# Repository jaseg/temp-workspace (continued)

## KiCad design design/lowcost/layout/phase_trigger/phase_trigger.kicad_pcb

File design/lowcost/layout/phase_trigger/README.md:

# Layout fragment: phase_trigger (trigger path, line driver, 16-tap phase delay line) - re-layout
`python3 gen_phase_trigger.py` -> `phase_trigger.kicad_pcb` (KiCad 7, 105.1 x 25.4 mm, own Edge.Cuts) and prints all tables and checks below.
`phase_trigger.png`: top = F.Cu without the pour (so widths show), silk, fab; below: F.Cu with pour, B.Cu (mirrored), In1, In2.
`phase_trigger_detail.png`: tap cells and one comparator, F.Cu red and B.Cu blue. Values: `sim/phase`, `sim/phase_array` RESULT.md, SPEC 4-6, 9.

## Stack-up (SPEC decision 9 rev., written into the board setup)
JLC04161H-7628 1.6 mm, checked on jlcpcb.com/impedance: F.Cu 35 um / 7628 0.2104 mm er 4.4 / In1 = solid GND / core 1.065 mm /
In2 = power (+2V5, +3V3, VTAP_N / VTAP_P strips) / 7628 0.2104 mm / B.Cu (GND pour, -2V5 and VSW_GND polygons, slow nets).
Mask er 3.8, 15 um on the trace. `microstrip()` = Hammerstad-Jensen + thickness correction + first-order mask term; `cpwg()` = Wadell.
| Line | width | Z0 | eps_eff | delay |
|---|---|---|---|---|
| 50 R (all 50 R nets, feeds, terminations) | **0.36 mm** (exact 0.360) | 50.0 R (51.0 R without mask) | 3.30 | 6.057 ps/mm |
| PSTRB_A/K sections, 73 R | **0.16 mm** (exact 0.159) | 72.8 R | 3.08 | 5.852 ps/mm |
| PH_LINE sections (width chosen for loaded 50 R) | **0.25 mm** (exact 0.251) | 60.1 R | 3.19 | 5.959 ps/mm |
Coplanar check: the side pour only lowers Z for gaps < 0.33 mm; pour gap used = 2 w (0.72 / 0.32 / 0.50 mm) -> microstrip, no correction.
Top pour keep-outs at 2 w around every RF segment and pad (script-verified on the filled pour); no pour between the strobe lines.
## Delay line (every cell generated by the same code, spread 0.000 ps)
| line | section | Z0 | load / tap | length / tap | unloaded | loaded | loaded Z |
|---|---|---|---|---|---|---|---|
| PSTRB_A/K | 0.16 mm straight | 72.8 R | 0.40 gate + 0.049 cap pad + 0.02 resistor fringe = 0.469 pF | **4.514 mm = pitch** | 26.4 ps | **40.0 ps** | 48.1 R |
| PH_LINE | 0.26 mm S-meander | 59.0 R | 0.37 gate + 0.026 pin-3 pad = 0.396 pF | **9.929 mm** | 59.3 ps | **70.0 ps** | 50.0 R |
PH_LINE targets 70 ps and the strobe lines 40 ps per tap (phase_array/RESULT: a 70 ps design measured 75.7 ps) -> expected ~75 ps real, 35 ps effective. The per-tap delays were raised from 65 / 35 ps so that the pitch (4.514 mm) leaves room for the meander: pin-3 pad edge to the nearest meander leg 0.52 mm, leg to leg 0.51 mm (was 0.02 / 0.244 mm). The 40 / 75 ps combination is not re-simulated.
Note: for a 70 ps section the trace that loads to 50 R is 60 R, not 73 R (73 R belonged to the 24 ps sections of phase/RESULT).
Cell: BAT15-04W, PH_LINE enters between pins 1/2 under the body and ends in pin 3 (zero-length tap), leaves pin 3 downward into an
S-meander (legs x = 1.00 / 1.99 / 2.76 mm, half-height 1.50 mm, same-net gaps >= 0.5 mm), 45-degree landing into the next diode. All on F.Cu
over In1, **no vias in any RF path**. Hold caps CA/CK vertical, node pad 0.29 mm from pin 1/2 (0.15 mm node trace), outer pad on the
strobe line. 1 k (to the comparator) and 2.2 k (to VTAP via In2) straddle each strobe line, perpendicular, either side of the cap.
**Summing node (symmetric)**: the A-side and K-side 1 k resistors are mirror images; each outer pad has a via (0.605 mm F.Cu) and the two
vias are joined by a straight B.Cu jumper (2 x 3.835 mm). The comparator input is tapped from the jumper MIDPOINT: a B.Cu branch runs
0.8 mm west of the jumper to its own via (4.166 mm), then F.Cu to the comparator pin. Both resistors therefore see the same path and stray
capacitance. Each COS3502 is centred between its two tap vias, so the routes to pins 1 and 3 are mirror images (3.849 mm each); the
script asserts channel A = channel B. One extra via per tap.
In1 cut-out under each hold node (VTAP strip in In2 below instead, symmetric A/K). K-side 1 k joins the A side on B.Cu (DC node).
COS3502 row behind PSTRB_A: pin 1 in line with the tap's 1 k, IN- via to the B.Cu VTH rail (R404 1 k / C404 100 n from VTAP_TH).

## Main chain (y = 0, in line, 0.3-0.35 mm pad gaps)
X1 BUF_OUT_T / J301 SMA (49.9 R R301 at U301.3) -> U301 TMUX136 -> TRIG_COM 3.0 mm -> U302 TLV3801 -> CMP_P / CMP_N as 2 x 50 R
(0.6 mm gap), R307 100 R bridging, R309/R310 470 R taps (LVDS_A under CMP_N on B.Cu) -> C308 -> U303 TRF37D73 -> bias tee -> C309 -> pi pad R311/R312/R313 -> 0.36 -> 0.25 mm step at x = -1.6 -> D01. PSTRB feeds from X2/X3
(50 R, 3.84 mm) step to 0.16 mm half a pitch before tap 0; far end 0.36 mm into 49.9 R (R401, R402, R403).
**Bias tee (revised, `sim/bias_tee/RESULT.md`, `bias_tee_detail.png` before/after)**: FB301 BLM15HD102 with pad 1 centred ON the line
-> 0.64 mm link -> L302 47 uH LQH32CN470K23L 1210 with R382 1 k beside it -> C314 100 nF across the cold pad (GND via at its pad) ->
+3V3 plane via pair beyond C314, TP306 on that row; C311/C312 moved 0.25 mm left to make room. Was 120 nH + 47 uH 0806 (on a 1008
land) + 100 n / 1 n beside it: 11 dB suck-out at 313 MHz, PRBS DDJ 17 ps rms; C313 (1 nF at the cold end, useless there) removed.
Necks: none (0.36 mm traces end on the WSON/UQFN pin centres with >= 0.19 mm to the neighbour pins).
Pad discontinuities (excess C vs line): 0402 in-line / T pads +28 fF, WSON/UQFN pins -11 fF, SOT-323 pin 3 +28 fF and hold-cap
pad +49 fF (both inside the tap load). SMA pin (1.27 mm): In1 cut-out below -> 70 R over 1.8 mm instead of +314 fF.

## Supplies and vias
Each supply pin -> 0.25-0.6 mm copper -> decoupling cap at the pin -> via pair to the In2 plane; -2V5 (TLV EP vias, R304, R306)
and VSW_GND (TMUX) as B.Cu polygons, VSW_GND pins also on a local F.Cu polygon; TRF EP 3 vias. Ground pads: one via beside
the pad. 182 vias: 46 GND, 69 supply, 67 signal (TAPn_IN, VTH, LVDS_A); **no stitching grid, no fences** (stitch after assembly).

**Changed vs previous**: JLC04161H-3313 -> 7628; all widths from the formula; PH_LINE moved from B.Cu (2 vias per tap) to an F.Cu meander; strobe 0.09 ->
0.16 mm (73 R now possible), pitch 3.815 -> 4.514 mm (40 ps per tap); compact in-line chain; no 90-degree corners; power via planes/polygons;
588 stitching vias removed; outline 106.8 x 24.6 -> 105.1 x 25.4 mm.

## Checks and open points
Script: bends <= 45 deg everywhere (corners at pad centres excepted), 0.1 mm copper clearance OK, passive courtyards OK, own
connectivity check 0 unrouted, RF pour clearance OK. 21 decoupling/chain parts sit inside the IC courtyard margin (pad gap >= 0.25 mm).
**kicad-cli 7 has no DRC**: run DRC in pcbnew after integration. U301 COM2 open on purpose.
Open: 40 / 75 ps per tap is not re-simulated (sim/phase_array used 35 / 70 ps); meander self-coupling is small at 0.5 mm gaps (2.4 h) but check by TDR.
Loaded strobe Z 45.5 R vs 49.9 R terminations (5 % reflection). Left 1 k inner pad of each node is over ground (~0.06 pF).
VTAP decoupling only at both ends of the In2 strips (DC rail behind 2.2 k). Corner WSON pins entered along x, not the pad axis.

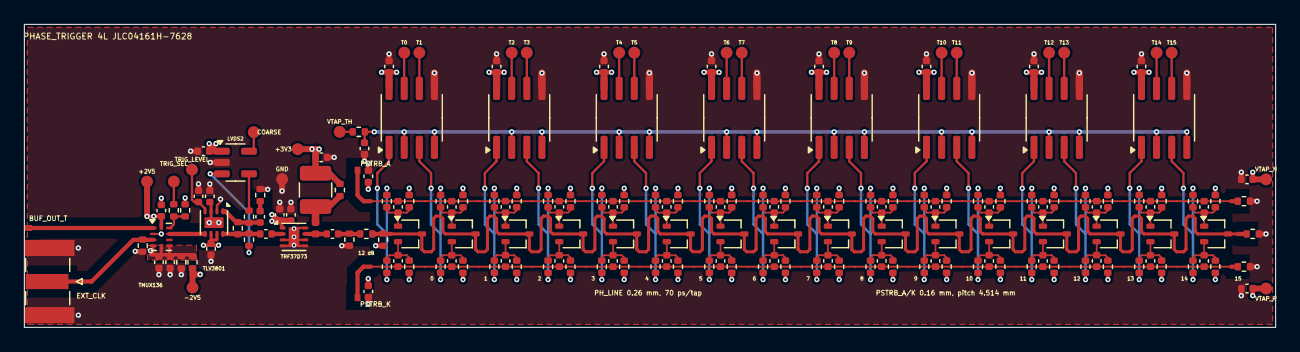
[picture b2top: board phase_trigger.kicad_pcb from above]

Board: 4 copper layers, 105.1 x 25.4 mm, 199 parts (0 on the bottom side), 92 nets.

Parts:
C30, C31, C32, C33, C34, C35, C36, C37, C301, C302, C304, C305, C310, C312, C314, C404: 100n; C_0402_1005Metric
C303, C311: 1n C0G; C_0402_1005Metric
C306: 10n; C_0402_1005Metric
C307, C308, C309: 1u; C_0402_1005Metric
CA00, CA01, CA02, CA03, CA04, CA05, CA06, CA07, CA08, CA09, CA10, CA11, CA12, CA13, CA14, CA15: 0.47p C0G; C_0402_1005Metric
CK00, CK01, CK02, CK03, CK04, CK05, CK06, CK07, CK08, CK09, CK10, CK11, CK12, CK13, CK14, CK15: 0.47p C0G; C_0402_1005Metric
CN00, CN15: 100n; C_0402_1005Metric
CP00, CP15: 100n; C_0402_1005Metric
D01, D02, D03, D04, D05, D06, D07, D08, D09, D10, D11, D12, D13, D14, D15, D16: BAT15-04W; SOT-323_SC-70
FB301: BLM15HD102; L_0402_1005Metric
J301: SMA EXT_CLK; SMA_Samtec_SMA-J-P-X-ST-EM1_EdgeMount
L302: 47u LQH32CN; L_1210_3225Metric
R301, R308, R401, R402, R403: 49.9; R_0402_1005Metric
R303: 1.5k; R_0402_1005Metric
R304: 2.7k; R_0402_1005Metric
R305: 10k; R_0402_1005Metric
R306: 18k; R_0402_1005Metric
R307: 100; R_0402_1005Metric
R309, R310: 470; R_0402_1005Metric
R311, R313: 82; R_0402_1005Metric
R312: 91; R_0402_1005Metric
R382, R404: 1k; R_0402_1005Metric
RNA00, RNA01, RNA02, RNA03, RNA04, RNA05, RNA06, RNA07, RNA08, RNA09, RNA10, RNA11, RNA12, RNA13, RNA14, RNA15: 2.2k; R_0402_1005Metric
RNK00, RNK01, RNK02, RNK03, RNK04, RNK05, RNK06, RNK07, RNK08, RNK09, RNK10, RNK11, RNK12, RNK13, RNK14, RNK15: 2.2k; R_0402_1005Metric
RSA00, RSA01, RSA02, RSA03, RSA04, RSA05, RSA06, RSA07, RSA08, RSA09, RSA10, RSA11, RSA12, RSA13, RSA14, RSA15: 1k; R_0402_1005Metric
RSK00, RSK01, RSK02, RSK03, RSK04, RSK05, RSK06, RSK07, RSK08, RSK09, RSK10, RSK11, RSK12, RSK13, RSK14, RSK15: 1k; R_0402_1005Metric
TP301, TP302, TP303, TP304, TP305, TP306, TP307, TP401, TP402, TP403, TP500, TP501, TP502, TP503, TP504, TP505, TP506, TP507, TP508, TP509, TP510, TP511, TP512, TP513, TP514, TP515: TestPoint_Pad_D1.0mm
U11, U12, U13, U14, U15, U16, U17, U18: COS3502; SOIC-8_3.9x4.9mm_P1.27mm
U301: TMUX136; Texas_UQFN-10_1.5x2mm_P0.5mm
U302: TLV3801; WSON-8-1EP_2x2mm_P0.5mm_EP0.9x1.6mm
U303: TRF37D73; WSON-8-1EP_2x2mm_P0.5mm_EP0.9x1.6mm
U304: SN65LVDS2; SOT-23-5
X1: IF_BUF_OUT_T
X2: IF_PSTRB_A
X3: IF_PSTRB_K

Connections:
+2V5: C301.1, C304.2, TP304.1, U301.10, U302.6, U302.7
+3V3: C30.1, C31.1, C32.1, C33.1, C34.1, C35.1, C36.1, C37.1, C310.2, C311.1, C312.1, C314.1, L302.2, R382.2, TP306.1, U11.8, U12.8, U13.8, U14.8, U15.8, U16.8, U17.8, U18.8, U303.1, U304.1
-2V5: C305.1, R304.1, R306.2, TP303.1, U302.3, U302.9
BUF_OUT_T: U301.1, X1.1
CMP_N: C307.1, R307.2, R310.1, U302.1
CMP_N_DUM: C307.2, R308.1
CMP_P: C308.1, R307.1, R309.2, U302.8
COARSE: TP305.1, U304.5
EXT_CLK: J301.1, R301.2, U301.3
GND: C30.2, C31.2, C32.2, C33.2, C34.2, C35.2, C36.2, C37.2, C302.1, C303.1, C304.1, C305.2, C306.2, C310.1, C311.2, C312.2, C314.2, C404.1, CN00.2, CN15.1, CP00.1, CP15.1, J301.2, R301.1, R303.1, R308.2, R311.1, R313.1, R401.2, R402.2, R403.2, TP307.1, U11.5, U12.5, U13.5, U14.5, U15.5, U16.5, U17.5, U18.5, U302.2, U303.3, U303.4, U303.5, U303.6, U303.8, U303.9, U304.2
LVDS_A: R309.1, U304.3
LVDS_B: R310.2, U304.4
PAD_IN: C309.2, R311.2, R312.1
PH_LINE: D01.3, D02.3, D03.3, D04.3, D05.3, D06.3, D07.3, D08.3, D09.3, D10.3, D11.3, D12.3, D13.3, D14.3, D15.3, D16.3, R312.2, R313.2, R401.1
PSTRB_A: CA00.2, CA01.2, CA02.2, CA03.2, CA04.2, CA05.2, CA06.2, CA07.2, CA08.2, CA09.2, CA10.2, CA11.2, CA12.2, CA13.2, CA14.2, CA15.2, R402.1, X2.1
PSTRB_K: CK00.1, CK01.1, CK02.1, CK03.1, CK04.1, CK05.1, CK06.1, CK07.1, CK08.1, CK09.1, CK10.1, CK11.1, CK12.1, CK13.1, CK14.1, CK15.1, R403.1, X3.1
TAP0: TP500.1, U11.7
TAP0_A: CA00.1, D01.1, RNA00.1, RSA00.1
TAP0_IN: RSA00.2, RSK00.1, U11.1
TAP0_K: CK00.2, D01.2, RNK00.2, RSK00.2
TAP1: TP501.1, U11.6
TAP1_A: CA01.1, D02.1, RNA01.1, RSA01.1
TAP1_IN: RSA01.2, RSK01.1, U11.3
TAP1_K: CK01.2, D02.2, RNK01.2, RSK01.2
TAP2: TP502.1, U12.7
TAP2_A: CA02.1, D03.1, RNA02.1, RSA02.1
TAP2_IN: RSA02.2, RSK02.1, U12.1
TAP2_K: CK02.2, D03.2, RNK02.2, RSK02.2
TAP3: TP503.1, U12.6
TAP3_A: CA03.1, D04.1, RNA03.1, RSA03.1
TAP3_IN: RSA03.2, RSK03.1, U12.3
TAP3_K: CK03.2, D04.2, RNK03.2, RSK03.2
TAP4: TP504.1, U13.7
TAP4_A: CA04.1, D05.1, RNA04.1, RSA04.1
TAP4_IN: RSA04.2, RSK04.1, U13.1
TAP4_K: CK04.2, D05.2, RNK04.2, RSK04.2
TAP5: TP505.1, U13.6
TAP5_A: CA05.1, D06.1, RNA05.1, RSA05.1
TAP5_IN: RSA05.2, RSK05.1, U13.3
TAP5_K: CK05.2, D06.2, RNK05.2, RSK05.2
TAP6: TP506.1, U14.7
TAP6_A: CA06.1, D07.1, RNA06.1, RSA06.1
TAP6_IN: RSA06.2, RSK06.1, U14.1
TAP6_K: CK06.2, D07.2, RNK06.2, RSK06.2
TAP7: TP507.1, U14.6
TAP7_A: CA07.1, D08.1, RNA07.1, RSA07.1
TAP7_IN: RSA07.2, RSK07.1, U14.3
TAP7_K: CK07.2, D08.2, RNK07.2, RSK07.2
TAP8: TP508.1, U15.7
TAP8_A: CA08.1, D09.1, RNA08.1, RSA08.1
TAP8_IN: RSA08.2, RSK08.1, U15.1
TAP8_K: CK08.2, D09.2, RNK08.2, RSK08.2
TAP9: TP509.1, U15.6
TAP9_A: CA09.1, D10.1, RNA09.1, RSA09.1
TAP9_IN: RSA09.2, RSK09.1, U15.3
TAP9_K: CK09.2, D10.2, RNK09.2, RSK09.2
TAP10: TP510.1, U16.7
TAP10_A: CA10.1, D11.1, RNA10.1, RSA10.1
TAP10_IN: RSA10.2, RSK10.1, U16.1
TAP10_K: CK10.2, D11.2, RNK10.2, RSK10.2
TAP11: TP511.1, U16.6
TAP11_A: CA11.1, D12.1, RNA11.1, RSA11.1
TAP11_IN: RSA11.2, RSK11.1, U16.3
TAP11_K: CK11.2, D12.2, RNK11.2, RSK11.2
TAP12: TP512.1, U17.7
TAP12_A: CA12.1, D13.1, RNA12.1, RSA12.1
TAP12_IN: RSA12.2, RSK12.1, U17.1
TAP12_K: CK12.2, D13.2, RNK12.2, RSK12.2
TAP13: TP513.1, U17.6
TAP13_A: CA13.1, D14.1, RNA13.1, RSA13.1
TAP13_IN: RSA13.2, RSK13.1, U17.3
TAP13_K: CK13.2, D14.2, RNK13.2, RSK13.2
TAP14: TP514.1, U18.7
TAP14_A: CA14.1, D15.1, RNA14.1, RSA14.1
TAP14_IN: RSA14.2, RSK14.1, U18.1
TAP14_K: CK14.2, D15.2, RNK14.2, RSK14.2
TAP15: TP515.1, U18.6
TAP15_A: CA15.1, D16.1, RNA15.1, RSA15.1
TAP15_IN: RSA15.2, RSK15.1, U18.3
TAP15_K: CK15.2, D16.2, RNK15.2, RSK15.2
TRF_BIAS: FB301.2, L302.1, R382.1
TRF_IN: C308.2, U303.2
TRF_OUT: C309.1, FB301.1, U303.7
TRIG_COM: U301.8, U302.5
TRIG_LEVEL: C306.1, TP302.1, U302.4
TRIG_SEL: R305.2, TP301.1
TRIG_SEL_S: R305.1, R306.1, U301.9
VSW_GND: C301.2, C302.2, C303.2, R303.2, R304.2, U301.2, U301.4, U301.5, U301.6
VTAP_N: CN00.1, CN15.2, RNA00.2, RNA01.2, RNA02.2, RNA03.2, RNA04.2, RNA05.2, RNA06.2, RNA07.2, RNA08.2, RNA09.2, RNA10.2, RNA11.2, RNA12.2, RNA13.2, RNA14.2, RNA15.2, TP402.1
VTAP_P: CP00.2, CP15.2, RNK00.1, RNK01.1, RNK02.1, RNK03.1, RNK04.1, RNK05.1, RNK06.1, RNK07.1, RNK08.1, RNK09.1, RNK10.1, RNK11.1, RNK12.1, RNK13.1, RNK14.1, RNK15.1, TP403.1
VTAP_TH: R404.1, TP401.1
VTH: C404.2, R404.2, U11.2, U11.4, U12.2, U12.4, U13.2, U13.4, U14.2, U14.4, U15.2, U15.4, U16.2, U16.4, U17.2, U17.4, U18.2, U18.4

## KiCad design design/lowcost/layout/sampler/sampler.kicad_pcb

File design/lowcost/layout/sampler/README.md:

# Layout fragment: sampler (bridge, hold amp, level shifter, sampler-strobe output)
`python3 gen_sampler.py` -> `sampler.kicad_pcb` (KiCad 7, 30.8 x 19.3 mm, own Edge.Cuts), plus the tables below and the checks.
`sampler.png`: top = F.Cu with the top pour hidden (so track widths show), silk, fab. Bottom row = F.Cu with pour, B.Cu (mirrored), In1.
`sampler_detail.png`: bridge, hold node, guard, STRB arms, balun. Values: `sim/sampler`, `sim/strobe`, `sim/phase_array` RESULT.md.

## Stack-up (SPEC decision 9 rev., written into the board setup)
JLC04161H-7628, 1.6 mm (checked on jlcpcb.com/impedance): L1 35 um / 7628 0.2104 mm er 4.4 / L2 In1 = solid GND /
core 1.065 mm er 4.6 / L3 In2 = +3V3 plane / 7628 0.2104 mm / L4 B.Cu (GND pour + slow feeds). Mask er 3.8, 15 um over the trace.
`microstrip()` in the script: Hammerstad-Jensen with Hammerstad thickness correction, plus a first-order mask overlay
(mask fills the air part of the fringing field, coefficient 1.2 c/h; it is an estimate that lands on JLC's 0.36 mm).
| Line | width | Z0 | eps_eff | delay |
|---|---|---|---|---|
| 50 R, all RF nets | **0.36 mm** (exact 0.360) | 50.0 R (51.0 R without mask) | 3.30 | **6.06 ps/mm** |
| neck inside the U402 pins 2/7 pads | 0.25 mm, 0.25 mm long (inside the pad) | 60 R | - | 1.5 ps |
| hold node (not a line, kept thin) | 0.15 mm | 75 R | - | 1.6 + 1.2 mm |
Top pour clearance from every RF trace = 2 w = 0.72 mm (3.4 h; keep-out rule areas per segment and per RF pad).
Coplanar check (Wadell CPWG): side ground only pulls Z below the microstrip value for gaps < 0.33 mm, so the lines are microstrip.

## RF nets (script table, all 0.36 mm / 50 R, F.Cu over In1, no vias, no layer changes)
| Net / segment | length | delay |
|---|---|---|
| BUF_OUT_S X1 -> R201, BRG_IN R201 -> D201.3 (under D201, between pins 1/2) | 0.80 + 3.12 mm | 4.8 + 18.9 ps |
| BRG_A / BRG_K rails (4 pieces, mirror images) | 2.565 mm each | 15.5 ps |
| STRB_A / STRB_K arms 47 pF -> balun (single-ended 50 R each; the bridge deck models no line, so 50 R) | 15.253 / 15.253 mm, mismatch 0 | 92.4 ps |
| STRB_CLIP balun.1 -> tap -> C404; TRF2_OUT C404 -> U402.7; TRF2_RFIN U402.2 -> C403; TRF2_IN C403 -> X2 | 2.97; 1.77; 0.83; 0.88 mm | |
| **Shorted stub**, 80 ps intended: 80 / 6.057 = 13.207 mm, drawn 13.207 mm (tap centre -> NT401) | 13.207 mm | **80.0 ps** |
Pad discontinuities (excess C vs the 0.36 mm line, noted instead of In1 cut-outs): 0402 in-line pads (R201, C403, C404) +28 fF,
R204 shunt pads on the arms +29 fF, balun pads +22 fF, SOT-323 pins +12 fF, D203 cathode +11 fF, X1/X2 +16 fF, WSON pins -11 fF.
All < 0.03 pF (about 1.5 ps of a 50 R line each); no compensation cut-outs needed.

## Placement (local origin = bridge centre, mirror axis y = 0, courtyards touching)
- X1 -> R201 10 R -> D201.3; D201 / D202 BAT15-04W side by side; rails meet at the 24.9 R pads; 47 pF C0G horizontal so the arms leave along the pad axis.
  1 k bias + 10 nF to VBIAS_A/K test pads. Arms: 45-degree chamfers, exact mirror images, R204 1 k on the arm pads at the balun.
- Hold: D202.3 -> U201.3 1.61 mm, C205 2.2 pF branch 1.18 mm. Guard (HOLD_FB, 0.1 mm) from U201 pin 4 under the body, between pins 2/3,
  around D202.3 / hold trace / C205.1 (between the C205 pads) to R208. Ground cut-out on In1/In2/B.Cu under the hold node, no top pour there.
- Supplies: U201 +2V5 pin -> 100 nF along the pad axis (0.6 mm copper), -2V5 pin -> via -> 100 nF on B.Cu under it; U202 +3V3 -> 100 nF (0.6 mm) -> In2 via;
  TRF37D73 VCC -> 1 nF + 100 nF in a row, via to In2.
- **Bias tee (revised, `sim/bias_tee/RESULT.md`, `bias_tee_detail.png` before/after)**: one straight chain perpendicular to the line,
  courtyards touching: FB402 BLM15HD102 with pad 1 centred ON the 50 R line (no stub; +32 fF, no In1 cut-out needed) -> 0.64 mm link
  -> L402 47 uH LQH32CN470K23L 1210 with R416 1 k 0402 beside it (two 45-degree links) -> C411 100 nF across the cold pad, GND via at
  its GND pad -> +3V3 plane via pair beyond C411 (supply enters through the capacitor) -> C412 10 uF on the via row.
  Was: bead 0.3 mm off the line on a 0.3 mm stub, plane vias at the inductor pad, 1 nF / 10 uF beside it on a polygon (-0.55 dB at 5.6 GHz).
  Ground pads: via right at the pad (not in it). U402 EP: 3 vias 0.2/0.45 in the EP (tented), GND pins tied to the EP.
- Strobe out, one straight line on y = -0.435: X2 -> C403 -> U402 TRF37D73 -> FB402 bias tee (bead pad centred on the line) -> C404 -> clip node
  -> T401 pin 1. **BAT15-03W clamp D203 added** (cathode on the clip node / stub tap, anode GND via), as `sim/phase_array/RESULT.md` asks.
- U202 level shifter below the K arm: R211 / C207 and C206 along the pad axes; the 1 k feedback R210 below, its OUT side via B.Cu.

## What changed (vs the JLC04161H-3313 version)
Stack-up 3313 -> 7628; RF width 0.17 -> 0.36 mm; full re-layout: compact courtyard-to-courtyard placement, only 45-degree bends,
wide/polygon supply connections, top pour with 2 w RF clearance, **no via stitching grid and no via fences** (to be added when the
fragments are assembled), clamp D203 added, stub re-computed (13.625 -> 13.207 mm), arms 17.26 -> 15.25 mm, board 31.5 x 22.8 -> 30.8 x 17.7 mm.
Vias left: 19 GND at pads/caps, 2 stub-short, 7 supply, 4 slow-signal (HOLD_OUT, SHIFT_OUT, -2V5 to B.Cu).

## Checks and limits
Script checks: courtyards (top and bottom) no overlap; copper clearance >= 0.1 mm; every bend <= 45 degrees; 0 unrouted after zone fill.
**kicad-cli 7 has no DRC**: run DRC in pcbnew after integration (net tie NT401 shorts the stub to GND on purpose).
Remaining deviations: R201 -> D201.3 is 3.12 mm (target <= 3 mm); BRG_IN passes 0.12 mm from the rail pads under D201; T-junctions at the
rail / R25 pads and at the stub tap / clamp; R210 and the D203 / C205 taps leave their pads sideways (short).
Open: balun pad map vs the Murata DLW21SN drawing; rail values follow the sampler RESULT (25 R / 47 pF); mask model is an estimate
(check with the JLC calculator at order time); integration must merge In2 (+3V3 here) with the board power split.

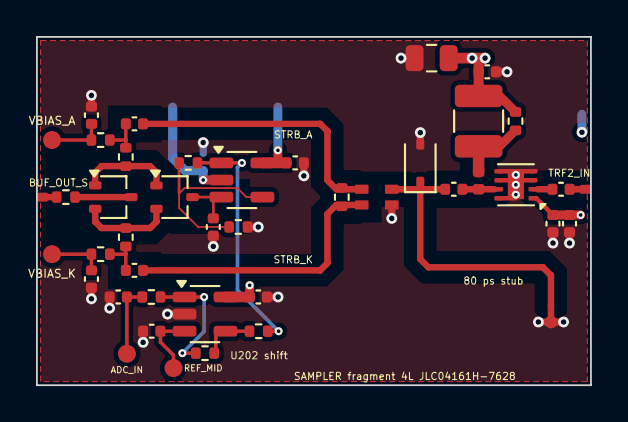
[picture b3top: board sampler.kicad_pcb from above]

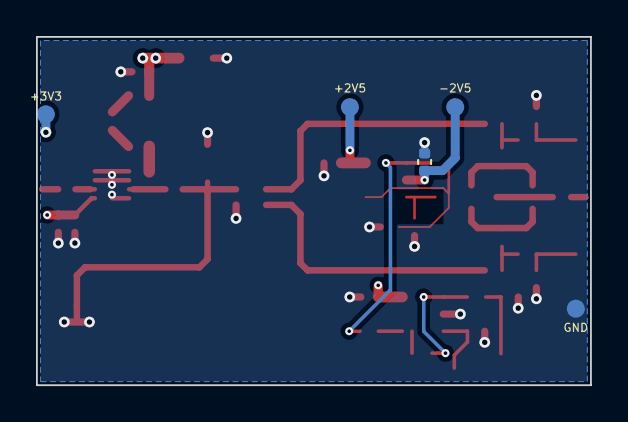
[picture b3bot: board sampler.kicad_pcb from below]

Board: 4 copper layers, 30.8 x 19.4 mm, 48 parts (5 on the bottom side), 26 nets.

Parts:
C201, C202: 47p C0G; C_0402_1005Metric
C203, C204, C206: 10n; C_0402_1005Metric
C205: 2.2p C0G; C_0402_1005Metric
C207: 220p C0G; C_0402_1005Metric
C208, C209, C210, C403, C404, C406, C411: 100n; C_0402_1005Metric
C405: 1n; C_0402_1005Metric
C412: 10u; C_0805_2012Metric
D201, D202: BAT15-04W; SOT-323_SC-70
D203: BAT15-03W; D_SOD-323
FB402: BLM15HD102; L_0402_1005Metric
L402: 47u LQH32CN; L_1210_3225Metric
NT401: NetTie_stub_short
R201: 10; R_0402_1005Metric
R202, R203: 24.9; R_0402_1005Metric
R204, R205, R206, R209, R210, R416: 1k; R_0402_1005Metric
R207: 1.00k 1%; R_0402_1005Metric
R208: 499 1%; R_0402_1005Metric
R211: 33; R_0402_1005Metric
T401: CMC_0805_balun
TP201, TP202, TP203, TP204, TP205, TP206, TP207, TP401: TestPoint_Pad_D1.0mm
U201, U202: TPH2501; SOT-23-5
U402: TRF37D73; WSON-8-1EP_2x2mm_P0.5mm_EP0.9x1.6mm
X1: IF_BUF_OUT_S
X2: IF_TRF2_IN

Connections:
+2V5: C208.1, TP204.1, U201.5
+3V3: C210.1, C405.2, C406.2, C411.1, C412.2, L402.2, R416.2, TP401.1, U202.5, U402.1
-2V5: C209.1, TP203.1, U201.2
ADC_IN: C207.2, R211.1, TP205.1
ADC_REF_MID: C206.2, TP206.1, U202.3
BIAS_A_N: C201.1, R202.2, R205.2
BIAS_K_N: C202.1, R203.1, R206.2
BRG_A: D201.1, D202.1, R202.1
BRG_IN: D201.3, R201.2
BRG_K: D201.2, D202.2, R203.2
BUF_OUT_S: R201.1, X1.1
GND: C203.2, C204.1, C205.1, C206.1, C207.1, C208.2, C209.2, C210.2, C405.1, C406.1, C411.2, C412.1, D203.2, NT401.2, R208.2, T401.3, TP207.1, U202.2, U402.3, U402.4, U402.5, U402.6, U402.8, U402.9
HOLD: C205.2, D202.3, U201.3
HOLD_FB: R207.1, R208.1, U201.4
HOLD_OUT: R207.2, R209.2, U201.1
SHIFT_IN: R209.1, R210.2, U202.4
SHIFT_OUT: R210.1, R211.2, U202.1
STRB_A: C201.2, R204.2, T401.2
STRB_CLIP: C404.1, D203.1, NT401.1, T401.1
STRB_K: C202.2, R204.1, T401.4
TRF2_BIAS: FB402.2, L402.1, R416.1
TRF2_IN: C403.2, X2.1
TRF2_OUT: C404.2, FB402.1, U402.7
TRF2_RFIN: C403.1, U402.2
VBIAS_A: C203.1, R205.1, TP201.1
VBIAS_K: C204.2, R206.1, TP202.1

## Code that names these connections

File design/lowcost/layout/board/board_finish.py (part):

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    txt("scope-fe rev A, 6L", 20.0, 55.6, 1.0)
    txt("SIG IN", 3.2, 7.3, 0.8)
    # review: "EXT CLK" was at y 46.6, 20 mm below J102 (y 26.5); no free silk room next to J102 (TP103 / TP104,
    # U304): its F.Fab value text EXT_CLK labels it (rule 9)
    # review: was (95.0, 19.65), over the D601 pads (silk_over_copper) and inside its outline: now north of J601
    txt("USB", 95.3, 7.7, 0.8)
    # block / connector labels (review): ANALOG comes from the analog block
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    # VTAP_P / VTAP_N: the mcuif interface stubs north of the R725 / R726 vias lead nowhere (board_power feeds the vias on L3)
    kill_seg("/VTAP_P", "B.Cu", (90.6, 45.85), (90.6, 45.0))
    kill_seg("/VTAP_N", "B.Cu", (92.45, 45.85), (92.45, 45.0))
    # VTH1 / VTH2 rails (L1) overhang their end pin stubs (vertical, from y 30.225 north) by 0.3 mm at both ends: each end
    # stub turns into the rail with a 45-degree bend instead (rail ends 0.2 mm inside the stub x, stub ends at y 27.95)
    for net, ends in (("/trigger_phase/VTH1", ((28.684, 0.3), (58.908, -0.3))),
                      ("/trigger_phase/VTH2", ((64.796, 0.3), (95.02, -0.3)))):
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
